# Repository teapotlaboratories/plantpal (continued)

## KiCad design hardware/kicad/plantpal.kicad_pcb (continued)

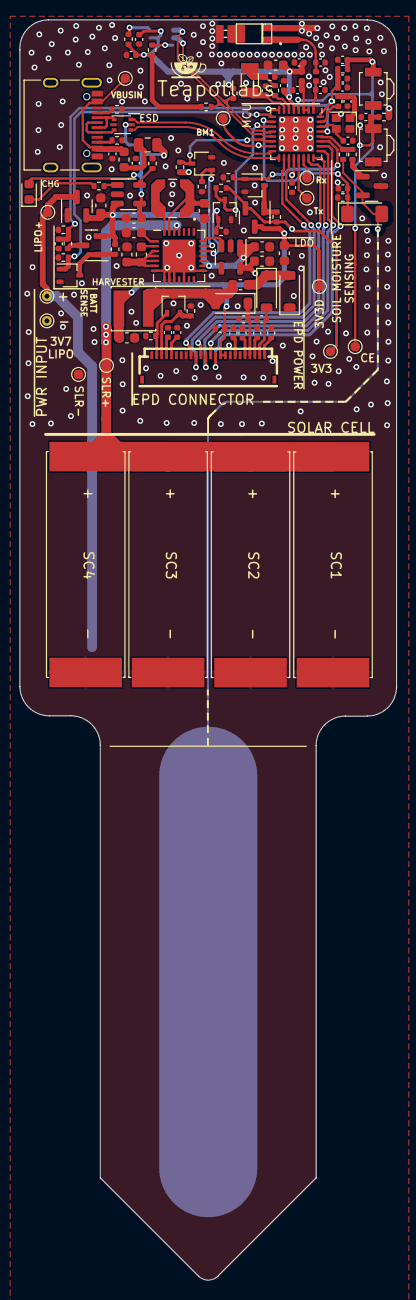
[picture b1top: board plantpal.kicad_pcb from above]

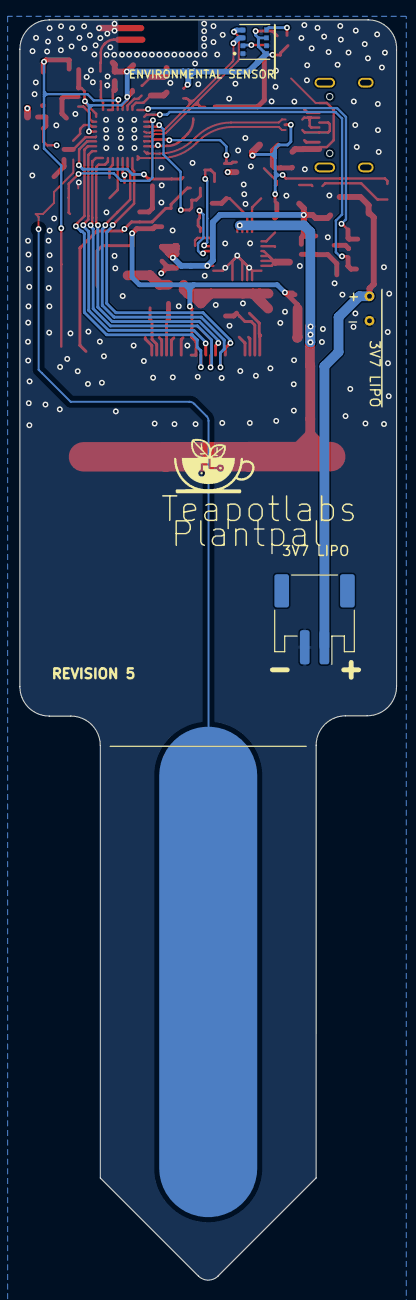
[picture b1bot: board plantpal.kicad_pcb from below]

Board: 4 copper layers, 38.4 x 128.5 mm, 119 parts (2 on the bottom side), 74 nets.

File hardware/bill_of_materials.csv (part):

Id,Designator,Quantity,Manufacturer,Manufacturer Part Number,Value,Part Description,Footprint,Type,Distributor,Distributor Part Number,Distributor Link,Datasheet
1,AE1,1,Walsin Technology Corporation,RFECA3216060A1T,RFECA3216060A1T,Chip RF Antenna 2.4GHz  2dBi,RFECA3216060A1T,SMD,Digikey,1292-1035-1-ND,https://www.digikey.com/en/products/detail/walsin-technology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,http://www.passivecomponent.com/wp-content/uploads/2018/10/A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
2,BT1,1,JST Sales America,S2B-PH-SM4-TB(LF)(SN),S2B-PH-SM4-TB(LF)(SN),Wire To Board Connector 1x2P PH 2mm Male 2A P=2mm,JST_PH_S2B-PH-SM4-TB_1x02-1MP_P2.00mm_Horizontal,SMD,LCSC,C295747,https://www.lcsc.com/product-detail/Wire-To-Board-Wire-To-Wi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,https://datasheet.lcsc.com/lcsc/2102031704_JST-Sales-America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
3,"C1, C2",2,Murata Electronics,GCM1555C1H120FA16D,12p,Ceramic Capacitors 50V 12pF C0G ±1%,0402_1005Metric,SMD,LCSC,C393682,https://www.lcsc.com/product-detail/Multilayer-Ceramic-Capac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,https://datasheet.lcsc.com/lcsc/2304140030_Murata-Electronic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
4,"C3, C4",2,Murata Electronics,GRM1555C1H100FA01D,10p,Ceramic Capacitors 50V 10pF C0G ±1%,0402_1005Metric,SMD,LCSC,C161520,https://www.lcsc.com/product-detail/Multilayer-Ceramic-Capac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,https://datasheet.lcsc.com/lcsc/1811081522_Murata-Electronic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
5,"C5, C19, C20, C23, C24, C25, C26",7,Samsung Electro-Mechanics,CL10A106KP8NNNC,10u,Ceramic Capacitor 10V 10uF X5R ±10% 0603,0603_1608Metric,SMD,LCSC,C19702,https://www.lcsc.com/product-detail/Multilayer-Ceramic-Capac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,https://datasheet.lcsc.com/lcsc/2304140030_Samsung-Electro-M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
6,"C6, C7, C10, C11, C13, C27, C28, C29",8,Samsung Electro-Mechanics,CL05B104KO5NNNC,100n,Ceramic Capacitor 16V 100nF X7R ±10%,0402_1005Metric,SMD,LCSC,C1525,https://www.lcsc.com/product-detail/Multilayer-Ceramic-Capac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,https://datasheet.lcsc.com/lcsc/2304140030_Samsung-Electro-M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
7,C8,1,YAGEO,CC0402KRX7R7BB103,10n,Ceramic Capacitors 16V 10nF X7R ±10%,0402_1005Metric,SMD,LCSC,C327009,https://www.lcsc.com/product-detail/Multilayer-Ceramic-Capac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,https://datasheet.lcsc.com/lcsc/1811141241_YAGEO-CC0402KRX7R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
8,"C9, C14, C31, C32, C33, C34, C35, C36, C37, C38, C39",11,Murata Electronics,GRM155Z71A105KE01D,1u,Ceramic Capacitors 10V 1uF X7R ±10%,0402_1005Metric,SMD,LCSC,C528974,https://www.lcsc.com/product-detail/Multilayer-Ceramic-Capac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,https://datasheet.lcsc.com/lcsc/2005261833_Murata-Electronic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
9,C17,1,YAGEO,CC0402KRX7R7BB103,10n,Ceramic Capacitors 16V 10nF X7R ±10%,0402_1005Metric,SMD,LCSC,C327009,https://www.lcsc.com/product-detail/Multilayer-Ceramic-Capac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,https://datasheet.lcsc.com/lcsc/1811141241_YAGEO-CC0402KRX7R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
10,C18,1,Samsung Electro-Mechanics,CL05B104KO5NNNC,100n,Ceramic Capacitor 16V 100nF X7R ±10%,0402_1005Metric,SMD,LCSC,C1525,https://www.lcsc.com/product-detail/Multilayer-Ceramic-Capac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,https://datasheet.lcsc.com/lcsc/2304140030_Samsung-Electro-M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
11,"C21, C22",2,Murata Electronics,GRM188R61A226ME15D,22u,Ceramic Capacitors 10V 22uF X5R ±20%,0603_1608Metric,SMD,LCSC,C84419,https://www.lcsc.com/product-detail/Multilayer-Ceramic-Capac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,https://www.mouser.com/datasheet/2/281/1/GRM188R61A226ME15_0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
12,C30,1,Samsung Electro-Mechanics,CL05B102KB5NNNC,1n,Ceramic Capacitors 50V 1nF X7R ±10%,0402_1005Metric,SMD,LCSC,C14442,https://www.lcsc.com/product-detail/Multilayer-Ceramic-Capac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,https://datasheet.lcsc.com/lcsc/2304140030_Samsung-Electro-M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
13,"C40, C41",2,Samsung Electro-Mechanics,CL10A475KA8NQNC,4u7,Ceramic Capacitors 25V 4.7uF X5R ±10%,0603_1608Metric,SMD,LCSC,C69335,https://www.lcsc.com/product-detail/Multilayer-Ceramic-Capac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,https://datasheet.lcsc.com/lcsc/1810261513_Samsung-Electro-M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
14,D1,1,Vishay Intertech,VLMO1300-GS08,VLMO1300-GS08,Orange 2V 20mA,0603_1608Metric,SMD,LCSC,C5184984,https://www.lcsc.com/product-detail/Light-Emitting-Diodes-LE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,https://datasheet.lcsc.com/lcsc/2209291030_Vishay-Intertech-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
15,D3,1,ST(Semtech),LL4148,LL4148,Switching Diode 75V 500mW 1V@10mA 4ns 0.2A,MiniMELF,SMD,LCSC,C9808,https://www.lcsc.com/product-detail/Switching-Diode_ST-Semte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,https://datasheet.lcsc.com/lcsc/2304140030_ST-Semtech-LL4148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
16,"D4, D5, D6",3,onsemi,MBR0530T1G,MBR0530,Schottky Barrier Diodes 30V 430mV@500mA 500mA,SOD-123,SMD,LCSC,C82046,https://www.lcsc.com/product-detail/Schottky-Barrier-Diodes-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,http://www.mccsemi.com/up_pdf/MBR0520~MBR0580(SOD123).pdf
17,F1,1,RUILON(Shenzhen Ruilongyuan Elec),SMD0805P075TF,0.75A,Resettable Fuses 6V 750mA 40A 1.5A,0805_2012Metric,SMD,LCSC,C20979,https://www.lcsc.com/product-detail/Resettable-Fuses_RUILON-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,https://datasheet.lcsc.com/lcsc/2304140030_RUILON-Shenzhen-R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
18,FB1,1,TDK,MMZ1608B601CTAH0,MMZ1608B601CTAH0,Ferrite Beads 400mΩ ±25% 600Ω@100MHz,0603_1608Metric,SMD,LCSC,C97120,https://www.lcsc.com/product-detail/Ferrite-Beads_TDK-MMZ160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,https://datasheet.lcsc.com/lcsc/2304140030_TDK-MMZ1608B601CT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
19,J1,1,XKB Connectivity,U262-161N-4BVC11,U262-161N-4BVC11,USB Connectors Type-C 3A USB 3.1 16P,XKB_U262-16XN-4BVC11,SMD,LCSC,C319148,https://www.lcsc.com/product-detail/USB-Connectors_XKB-Conne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,https://datasheet.lcsc.com/lcsc/2110151630_XKB-Connectivity-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
20,J4,1,HCTL,HC-FPC-05-09-24RLTAG,HC-FPC-05-09-24RLTAG,FFC & FPC Connectors Clamshell 24P Bottom Contact P=0.5mm,FPC-SMD_24P-P0.50_HC-FPC-05-09-24RLTAG,SMD,LCSC,C5213757,https://www.lcsc.com/product-detail/FFC-FPC-Connectors_HCTL-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,https://datasheet.lcsc.com/lcsc/2210261730_HCTL-HC-FPC-05-09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
21,L1,1,Murata Electronics,LQW15AN2N2G80D,2n2,Power Inductors 2.53A 2.2nH ±2%,0402_1005Metric,SMD,LCSC,C412264,https://www.lcsc.com/product-detail/Power-Inductors_Murata-E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,https://datasheet.lcsc.com/lcsc/2304140030_Murata-Electronic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
22,L2,1,UNI-ROYAL(Uniroyal Elec),0402WGF0000TCE,0,Resistor 62.5mW ±1% 0Ω,0402_1005Metric,SMD,LCSC,C17168,https://www.lcsc.com/product-detail/Chip-Resistor-Surface-Mo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,https://datasheet.lcsc.com/lcsc/2206010216_UNI-ROYAL-Uniroya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
23,L3,1,Coilcraft,LPS4012-103MRC,10u 0.55A,Power Inductors - SMD 10uH Shld 20% 1.1A 350 mOhms,LPS4012-103MRB,SMD,Mouser,994-LPS4012-103MRC,https://www.mouser.com/ProductDetail/Coilcraft/LPS4012-103MR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,https://www.mouser.com/datasheet/2/597/lps4012-1890589.pdf
24,L4,1,TDK,MLZ1608M100WT000,10u,Power Inductors 10uH ±20% 90mA 1.05Ω,0603_1608Metric,SMD,LCSC,C76798,https://www.lcsc.com/product-detail/Inductors-SMD_TDK-MLZ160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,https://product.tdk.com/system/files/dam/doc/product/inducto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
25,L5,1,cjiang (Changjiang Microelectronics Tech),FNR4012S100MT,10u 1A,"Power Inductors 1A 10uH ±20% 1.1A SMD,4x4mm ",FNR4012S,SMD,LCSC,C167785,https://www.lcsc.com/product-detail/Power-Inductors_cjiang-C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,https://datasheet.lcsc.com/lcsc/2304140030_cjiang--Changjian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
26,"Q1, Q2, Q5, Q9",4,Diodes Incorporated,DMG1012UW-7,DMG1012UW,"MOSFET N Channel 20V 1A 450mΩ@4.5V,600mA 290mW ",SOT-323_SC-70,SMD,LCSC,C156390,https://www.lcsc.com/product-detail/MOSFETs_Diodes-Incorpora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,https://datasheet.lcsc.com/lcsc/1806090918_Diodes-Incorporat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
27,Q3,1,"Jiangsu Changjing Electronics Technology Co., Ltd.",MMBT3906 2A,MMBT3906,"Bipolar Transistors 40V 200mW 100@10mA,1V 200mA PNP",SOT-23,SMD,LCSC,C2143,https://www.lcsc.com/product-detail/Bipolar-Transistors-BJT_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,https://datasheet.lcsc.com/lcsc/1809211015_Jiangsu-Changjing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
28,"Q4, Q8",2,TECH PUBLIC,PMV32UP,PMV32UP,MOSFET P Channel 20V 4A 52mΩ@4.5V,SOT-23,SMD,LCSC,C2959851,https://www.lcsc.com/product-detail/MOSFETs_TECH-PUBLIC-PMV3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,https://datasheet.lcsc.com/lcsc/2201211500_TECH-PUBLIC-PMV32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
29,Q6,1,Alpha & Omega Semicon,AO3407A,AO3407A,"MOSFET P Channel 30V 4.3A 48mΩ@10V,4.3A 1.4W",SOT-23,SMD,LCSC,C15155,https://www.lcsc.com/product-detail/MOSFETs_Alpha-Omega-Semi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,https://datasheet.lcsc.com/lcsc/1810231523_Alpha---Omega-Sem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
30,Q7,1,Vishay Intertech,SI1308EDL-T1-GE3,SI1308EDL,"MOSFET N Channel 30V 1.4A 132mΩ@10V,1.4A ",SOT-323_SC-70,SMD,LCSC,C469327,https://www.lcsc.com/product-detail/MOSFETs_Vishay-Intertech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,https://datasheet.lcsc.com/lcsc/1912202016_Vishay-Intertech-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

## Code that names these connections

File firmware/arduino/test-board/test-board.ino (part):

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#define SM_PWM_DUTY_CYCLE 4

/* Battery Measurement */
#define BATT_MEAS_PIN 2
#define BATT_MEAS_EN_PIN 3
#define BATT_MEAS_VD_R1 4700.0  // 4.7K ohm
#define BATT_MEAS_VD_R2 10000.0 // 10K Ohm

/* AEM10941 Pin Status */
#define MPP_STATUS_PIN 5
#define PWR_STATUS_PIN 8

/* User button */
#define USER_BUTTON_PIN 9
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  digitalWrite( SM_PWM_PIN, LOW );

  /* Initialise Battery Measurement */
  pinMode( BATT_MEAS_PIN, INPUT );
  pinMode( BATT_MEAS_EN_PIN, OUTPUT );
  digitalWrite( BATT_MEAS_EN_PIN, LOW );

  /* Initialise AEM10941 Status Pin */
  pinMode( MPP_STATUS_PIN, INPUT );
  pinMode( PWR_STATUS_PIN, INPUT );

  /* Initialise User Button */
  pinMode( USER_BUTTON_PIN, INPUT );

  /* Setup interrupt for counting AEM pin status and user button */
  attachInterrupt(digitalPinToInterrupt(PWR_STATUS_PIN), process_power_status, FALLING);
  attachInterrupt(digitalPinToInterrupt(MPP_STATUS_PIN), process_mpp_status, FALLING);
  attachInterrupt(digitalPinToInterrupt(USER_BUTTON_PIN), process_user_button, FALLING);

  /* Deep-sleep now */
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
  // Assert signal is inverse, caused by the 
  // MPP status driver ( see schematics )
  return !digitalRead( MPP_STATUS_PIN );
}

uint8_t ReadPowerStatus()
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
  // Assert signal is inverse, caused by the 
  // power status driver ( see schematics )
  return !digitalRead( PWR_STATUS_PIN );
}

uint8_t ReadUserButton()
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
uint16_t ReadBatteryMillivolts()
{ 
  digitalWrite( BATT_MEAS_EN_PIN, HIGH );
  delay(20); // wait until voltage is stable
  uint16_t batt_vd = analogReadMilliVolts( BATT_MEAS_PIN );
  digitalWrite( BATT_MEAS_EN_PIN, LOW );
  
  // calculate battery voltage based 
  // on voltage divider resistor
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
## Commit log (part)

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2023-09-21 add ext crystal and rtc crystal
2023-09-22 add esp32, usb, charger, power gate, and soil moisture
2023-09-22 separate schematics
2023-09-22 fix label
2023-09-22 schematic restructure update
2023-09-23 beautify schematic
2023-09-23 first pass schematic and new fpc symbol
2023-09-23 add library
2023-09-23 solar power schematic done
2023-09-23 usb power schematic partially done
2023-09-24 usb power schematic done
2023-09-24 battery schematic done
2023-09-24 clean-up
2023-09-24 power gate reg partially done
2023-09-24 power gate reg done
2023-09-24 partial work on main controller schematic
2023-09-24 add chip antenna fp
2023-09-24 update work on main controller
2023-09-24 update library
2023-09-24 wip main controller schematic
2023-09-24 main controller sch done
2023-09-24 sensor sch partially done
2023-09-24 sensor sch done
2023-09-24 change resistor to 0402
2023-09-24 update note
2023-09-24 add fpc 24 connector
2023-09-24 add chip antenna model
2023-09-24 display sch done
2023-09-24 add power inductor 10uh 1A
2023-09-24 update fottprint
2023-09-24 add B3u-3000P model and fp
2023-09-24 update button fp
2023-09-24 update fp and models libraru
2023-09-24 update main controller
2023-09-26 partially group components
2023-09-27 change rf antenna rf matching inductor to 0402
2023-09-28 group components
2023-09-30 wip pcb
2023-09-30 move soil sensor pin and add it to main pcb
2023-09-30 add default configuration
2023-10-01 add gnd for matching rf radio
2023-10-01 change batt footprint
2023-10-01 work in progress
2023-10-01 change usb polarity
2023-10-02 update 3d model file
2023-10-03 update 3d model
2023-10-03 add testpad and wip
2023-10-03 add testpin for chip_enable
2023-10-04 wip wake-up button
2023-10-04 wip wake up button
2023-10-06 improve usb trace
2023-10-06 change charge rate to 1A
2023-10-06 add assembly production
2023-10-06 add production file
2023-10-07 add fpc library and models
2023-10-07 change fpc connector
2023-10-07 update bom
2023-10-07 add jst battery
2023-10-07 update production file
2023-10-07 remove via in pad
2023-10-07 update production assembly image
2023-10-17 hardware/kicad/battery.kicad_sch
2023-10-17 update docs to rev 2
2023-10-24 update production for revision 2
2023-10-24 add interactive bom
2023-10-24 update incorrect D1 value
2024-01-04 add display test
2024-01-04 fix D6 polarity
2024-01-04 wip: removing powergate
2024-01-04 wip: revision 2
2024-01-05 add test code
2024-01-05 add happy face graphics
2024-01-05 update test example
2024-01-06 add simple-monitor example
2024-01-06 update test-board example
2024-01-06 update firmware
2024-01-07 re-route sense out, add display power switch
2024-01-11 revision 3 prod
2024-01-12 add readme and schematics for documentation
2024-01-12 add additiontal documents
2024-01-15 upload docs
2024-01-15 changed to git lfs
2024-01-17 update doc
2024-01-17 update docs
2024-01-17 fix schematic info
2024-01-17 add git attributes for git lfs
2024-01-18 add case_render.gif
2024-01-18 increase case_render.gif size
2024-02-02 re-wire epd power
2024-02-02 update lfs object
2024-02-02 clean-up rewire
2024-02-02 rewire epd power
2024-02-03 update revision silkscreen to 4
2024-02-03 add pin 1 indicator for inductor
2024-02-03 update to revision 4
2024-02-03 add case
2024-02-03 remove system file
2024-02-03 add image for documentation
2024-02-06 add simple wifi mqtt publish
2024-02-06 update example to revision 4 board
2024-02-12 add deep-sleep test
2024-02-13 add code for power testing
2024-02-13 update simple monitor to use rev 4
2024-02-13 add docs
2024-02-13 add measurement docs
2024-02-14 add readme
2024-02-21 add video for docs
2024-02-21 add video
2024-04-06 update to kicad 8
2024-04-07 update silkscreen
2024-04-15 change antenna trace width to latest pcb stack-up
2024-04-18 Revision 5
2024-06-06 update test board code
2024-06-06 update test code
2024-07-09 update docs with resin images
2024-07-14 update docs file
2024-07-14 add wiki docs
2024-07-14 update gitattributes
2024-07-14 restore readme from lfs
